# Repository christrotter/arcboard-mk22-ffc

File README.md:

# arcboard-mk22-ffc

FFC wiring harness for the Arcboard mk22's [mainboard](https://github.com/christrotter/arcboard-stm32-mk2).  Hooks up a whole pile of keys, peripherals, and indicators with a single cable.  

The goal was to reduce manual soldering as much as possible while also reducing the number of FFC's coming off the mainboard.  [The old mainboard](https://github.com/christrotter/arcboard-stm32) had 10 FFCs coming off at all angles and it was a nightmare to install.

All questions, and more, answered here: 
[Walking through the process of making a custom FFC.](https://docs.google.com/document/d/1AaeZN3C4SzMbZbiK-B96kASK0Lhcgzr27FD6T2ESAdA/edit?usp=sharing)

And if you're interested in learning more about the board itself:
[The mk22 build journal - in great detail.](https://docs.google.com/document/d/1yYdNSWEpefUsuglO4ZzcITcItB_Wx3liXkT57BLO2Ac/edit?usp=sharing)

# ordering
See the 'making a custom FFC' doc for great detail on this.

The different pitch sizes require different total FFC thicknesses.
- 0.3mm-pitch -> 0.2mm thick FFC, including stiffener
- 0.5mm-pitch -> 0.3mm thick FFC, including stiffener (connector specs range from `0.27-0.33mm` to `0.29-0.31mm`)

## peripherals
But what peripherals does this hook up?
- six [Cyboard column PCBs](https://cyboard.digital/products/dactyl-flex-pcbs)
- five [Cyboard thumb key PCBs](https://cyboard.digital/products/dactyl-flex-pcbs)
- [main LED indicator PCB](https://github.com/christrotter/para-led-ogram)
- [ring gear encoder indicator PCB](https://github.com/christrotter/ring-led-pcb)
- [an ST7789v2 LCD adapter PCB](https://github.com/christrotter/lcd-adapter-pcb)
- [two led-backlit EC10 encoders](https://github.com/christrotter/top-encoder-pcb)
- [one non-lit EC10 encoder](https://github.com/christrotter/mouse-encoder-pcb)
- [STM32 mainboard](https://github.com/christrotter/arcboard-stm32)
- [a dpad (5-way)](https://github.com/christrotter/led-pad)
- [three paddles (3x 5-way)](https://github.com/christrotter/multi-paddle-pcb)
- [PMW3360 to FFC](https://github.com/christrotter/charybdis-pmw-3360-sensor-pcb/tree/arcboarding) (*forked from* [Charybdis](https://github.com/Bastardkb/charybdis-pmw-3360-sensor-pcb))

### what if only one half has a trackball?
The theory is I tape or cap off the PMW endpoint on the left half.

## schematic

## PCB layout

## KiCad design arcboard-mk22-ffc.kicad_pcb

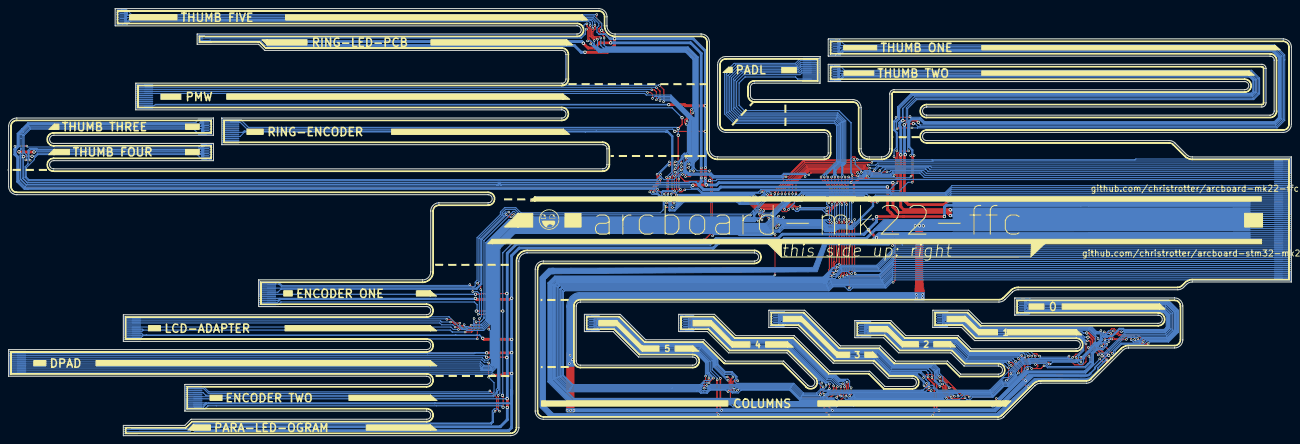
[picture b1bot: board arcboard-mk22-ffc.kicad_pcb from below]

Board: 2 copper layers, 313.0 x 104.2 mm, 23 parts (11 on the bottom side), 53 nets.

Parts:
COL3: Conn_01x13; FFC Termination 13x0.3 ECT818001568
COL-0, COL-1, COL-2, COL-4, COL-5: Conn_01x13; FFC Termination 13x0.3 ECT818001568
DPAD1: Conn_01x12; ffc-terminator-12pin_0.5mm
ENC1, ENC2, ENC3: Conn_01x12; ffc-terminator-12pin_0.5mm
J7, J8: Conn_01x04; ffc-terminator-4pin_0.5mm
J10: Conn_01x60; FFC-termination-60p-0.5mm
LCD1: Conn_01x12; ffc-terminator-12pin_0.5mm
LOGO1, LOGO1#2: **REF; awesome-logo
PADDLE1: Conn_01x12; ffc-terminator-12pin_0.5mm
PMW1: Conn_01x12; ffc-terminator-12pin_0.5mm
ROW0-0, ROW0-1, ROW0-2, ROW0-3, ROW0-4: Conn_01x13; FFC Termination 13x0.3 ECT818001568

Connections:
+3V3: ENC1.1, ENC2.1, ENC3.12, J10.50, PMW1.1
+5V: COL3.8, COL3.9, COL-0.8, COL-0.9, COL-1.8, COL-1.9, COL-2.8, COL-2.9, COL-4.8, COL-4.9, COL-5.8, COL-5.9, DPAD1.10, ENC1.6, ENC2.6, J7.2, J8.2, J10.20, J10.21, J10.22, J10.23, J10.24, J10.37, J10.38, J10.39, J10.40, J10.41, ROW0-0.2, ROW0-0.3, ROW0-0.4, ROW0-0.5, ROW0-1.2, ROW0-1.3, ROW0-1.4, ROW0-1.5, ROW0-2.2, ROW0-2.3, ROW0-2.4, ROW0-2.5, ROW0-3.2, ROW0-3.3, ROW0-3.4, ROW0-3.5, ROW0-4.2, ROW0-4.3, ROW0-4.4, ROW0-4.5
COL0: COL-0.4, DPAD1.6, J10.12, ROW0-0.12
COL1: COL-1.4, DPAD1.5, J10.13, PADDLE1.1, ROW0-1.12
COL2: COL-2.4, DPAD1.4, J10.14, PADDLE1.2, ROW0-2.12
COL3: COL3.4, DPAD1.3, J10.15, PADDLE1.3, ROW0-3.12
COL4: COL-4.4, DPAD1.2, J10.16, PADDLE1.4, ROW0-4.12
COL5: COL-5.4, J10.17, PADDLE1.5
DPAD_DI: DPAD1.9, ENC1.12
DPAD_DO: DPAD1.8, ENC2.11
ENC1_DI: ENC1.11, J7.4
ENC2_DO: ENC2.12, J8.3
ENCODER1_R1: ENC1.9, J10.47
ENCODER1_R2: ENC1.7, J10.46
ENCODER2_R1: ENC2.9, J10.45
ENCODER2_R2: ENC2.7, J10.44
ENCODER3_R1: ENC3.6, J10.43
ENCODER3_R2: ENC3.4, J10.42
GND: COL3.6, COL3.7, COL-0.6, COL-0.7, COL-1.6, COL-1.7, COL-2.6, COL-2.7, COL-4.6, COL-4.7, COL-5.6, COL-5.7, DPAD1.1, DPAD1.11, DPAD1.12, ENC1.2, ENC1.3, ENC1.4, ENC2.2, ENC2.3, ENC2.4, ENC3.11, J7.1, J8.1, J10.25, J10.26, J10.27, J10.28, J10.29, J10.30, J10.31, J10.32, J10.33, J10.34, J10.35, J10.36, LCD1.2, LCD1.3, LCD1.4, PADDLE1.11, PMW1.2, ROW0-0.6, ROW0-0.7, ROW0-0.8, ROW0-0.9, ROW0-0.10, ROW0-1.6, ROW0-1.7, ROW0-1.8, ROW0-1.9, ROW0-1.10, ROW0-2.6, ROW0-2.7, ROW0-2.8, ROW0-2.9, ROW0-2.10, ROW0-3.6, ROW0-3.7, ROW0-3.8, ROW0-3.9, ROW0-3.10, ROW0-4.6, ROW0-4.7, ROW0-4.8, ROW0-4.9, ROW0-4.10
KEYS_DI: COL-5.11, J10.19
KEYS_DO: COL-0.2, ROW0-4.1
LCD_3V3: J10.59, LCD1.1
LCD_BL: J10.58, LCD1.5, LCD1.6
LCD_CS: J10.57, LCD1.10
LCD_DC: J10.56, LCD1.9
LCD_RST: J10.55, LCD1.7
Main_LED_OUT: J8.4, J10.18
unnamed: COL-0.11, COL-1.2
unnamed: COL-1.11, COL-2.2
unnamed: COL3.2, COL-2.11
unnamed: COL3.11, COL-4.2
unnamed: COL-4.11, COL-5.2
unnamed: ROW0-0.1, ROW0-1.11
unnamed: ROW0-1.1, ROW0-2.11
unnamed: ROW0-2.1, ROW0-3.11
unnamed: ROW0-3.1, ROW0-4.11
PARA_DI: J7.3, ROW0-0.11
PMW_CS: J10.52, PMW1.10
PMW_MOTION: J10.51, PMW1.9
ROW0: J10.1, ROW0-0.13, ROW0-1.13, ROW0-2.13, ROW0-3.13, ROW0-4.13
ROW1: COL3.10, COL-0.10, COL-1.10, COL-2.10, COL-4.10, COL-5.10, J10.2
ROW2: COL3.12, COL-0.12, COL-1.12, COL-2.12, COL-4.12, COL-5.12, J10.3
ROW3: COL3.13, COL-0.13, COL-1.13, COL-2.13, COL-4.13, COL-5.13, J10.4
ROW4: COL3.1, COL-0.1, COL-1.1, COL-2.1, COL-4.1, COL-5.1, J10.5
ROW5: COL3.3, COL-0.3, COL-1.3, COL-2.3, COL-4.3, COL-5.3, J10.6
ROW6: COL3.5, COL-0.5, COL-1.5, COL-2.5, COL-4.5, COL-5.5, J10.7
ROW7: J10.8, PADDLE1.6
ROW8: J10.9, PADDLE1.7
ROW9: J10.10, PADDLE1.8
ROW10: DPAD1.7, J10.11
SPI1_CLK: J10.54, LCD1.12, PMW1.12
SPI1_MISO: J10.60, PMW1.11
SPI1_MOSI: J10.53, LCD1.11, PMW1.8

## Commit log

2026-05-30 finished tracing
2026-05-30 fixing folding issues, fattening up the led boards
2026-05-30 fixing more cray, starting silkscreen
2026-05-30 first draft silkscreen
2026-06-06 silkscreen changes, cleanup prior to easy-eda
2026-06-06 silkscreen changes, fixing drc issues
2026-06-06 first draft readme
2026-06-07 adding correct stiffener length reminders
2026-06-19 fixing 0.3 footprint, the di-do mixup, and starting user comments updates
2026-06-19 created stiffener layers, updated footprints and comments
2026-06-19 fixing the reversed pinouts for pmw and lcd-adapter
2026-06-20 updating ring-led-pcb pinouts
2026-06-20 fixing silkscreen
2026-06-20 ordered this
2026-06-23 updating readme and images
